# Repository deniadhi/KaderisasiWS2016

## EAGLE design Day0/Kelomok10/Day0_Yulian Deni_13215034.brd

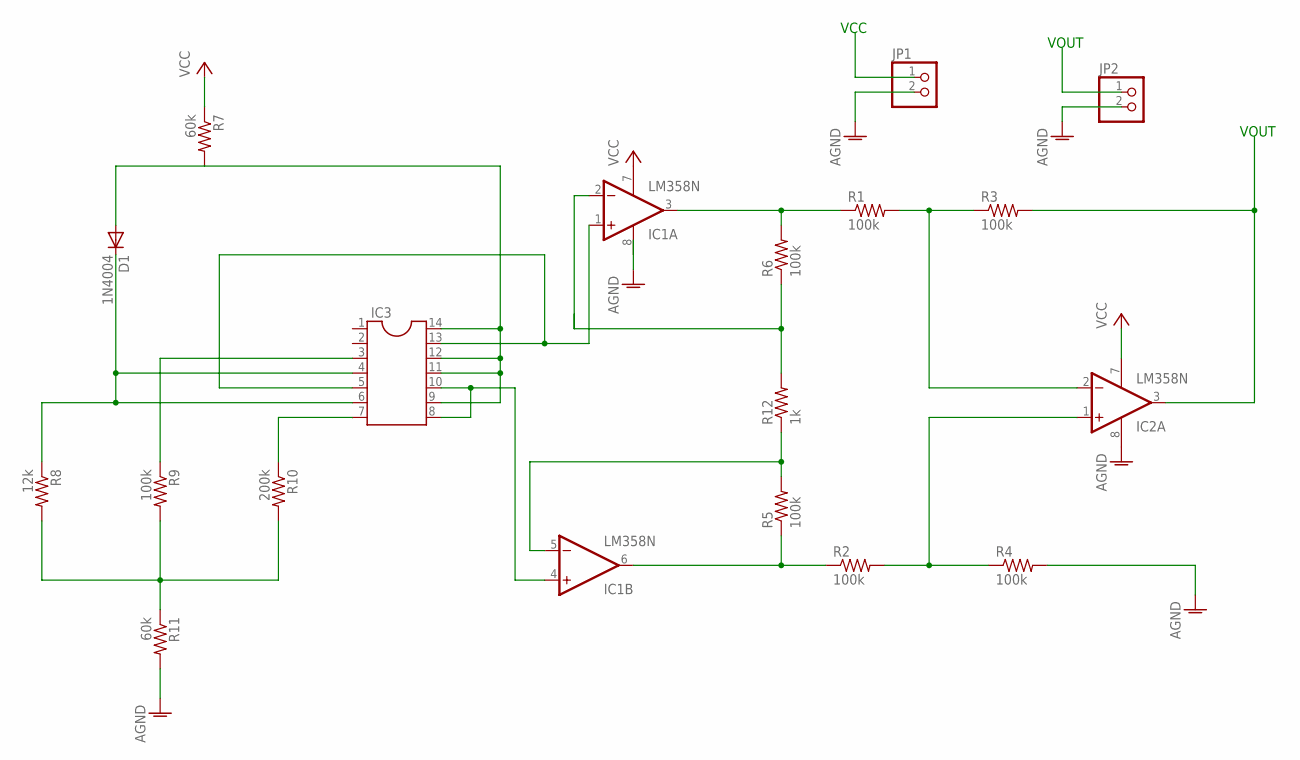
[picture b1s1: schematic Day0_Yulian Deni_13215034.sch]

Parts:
D1: 1N4004; DO41-10
IC1, IC2: LM358N; DIL08
IC3: DIL14
JP1, JP2: PINHD-1X2; 1X02
R1, R2, R3, R4, R5, R6, R9: 100k; 0204/7
R7, R11: 60k; 0204/7
R8: 12k; 0204/7
R10: 200k; 0204/7
R12: 1k; 0204/7

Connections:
AGND: IC2.8 (V-), JP1.2, JP2.2, R4.2, R11.2
unnamed: D1.A, IC3.9, IC3.11, IC3.12, IC3.14, R7.2
unnamed: D1.C, IC3.4, IC3.6, R8.1
unnamed: IC3.7, R10.1
unnamed: IC1.1 (+IN), IC3.5, IC3.13
unnamed: IC3.3, R9.1
unnamed: R8.2, R9.2, R10.2, R11.1
unnamed: IC1.4 (+IN), IC3.8, IC3.10
unnamed: IC1.3 (OUT), R1.1, R6.2
unnamed: R6.1, R12.2
unnamed: IC1.5 (-IN), R5.2, R12.1
unnamed: IC1.6 (OUT), R2.1, R5.1
unnamed: IC2.2 (-IN), R1.2, R3.1
unnamed: IC2.1 (+IN), R2.2, R4.1
unnamed: IC2.3 (OUT), R3.2
V-: IC1.8 (V-)
VCC: IC1.7 (V+), IC2.7 (V+), R7.1

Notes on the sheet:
VOUT
VCC

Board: 2 copper layers, 18 parts (0 on the bottom side), 16 nets, no tracks yet.

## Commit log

2016-09-23 Create Kelompok 10
2016-09-23 Create aaaa
2016-09-23 Create empty
    empty
2016-09-24 Create Kelompok10
